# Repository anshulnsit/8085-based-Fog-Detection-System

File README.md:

# 8085-based-Fog-Detection-System
A Fog Detection system made with Intel 8085 microprocessor as EC - 316 Project

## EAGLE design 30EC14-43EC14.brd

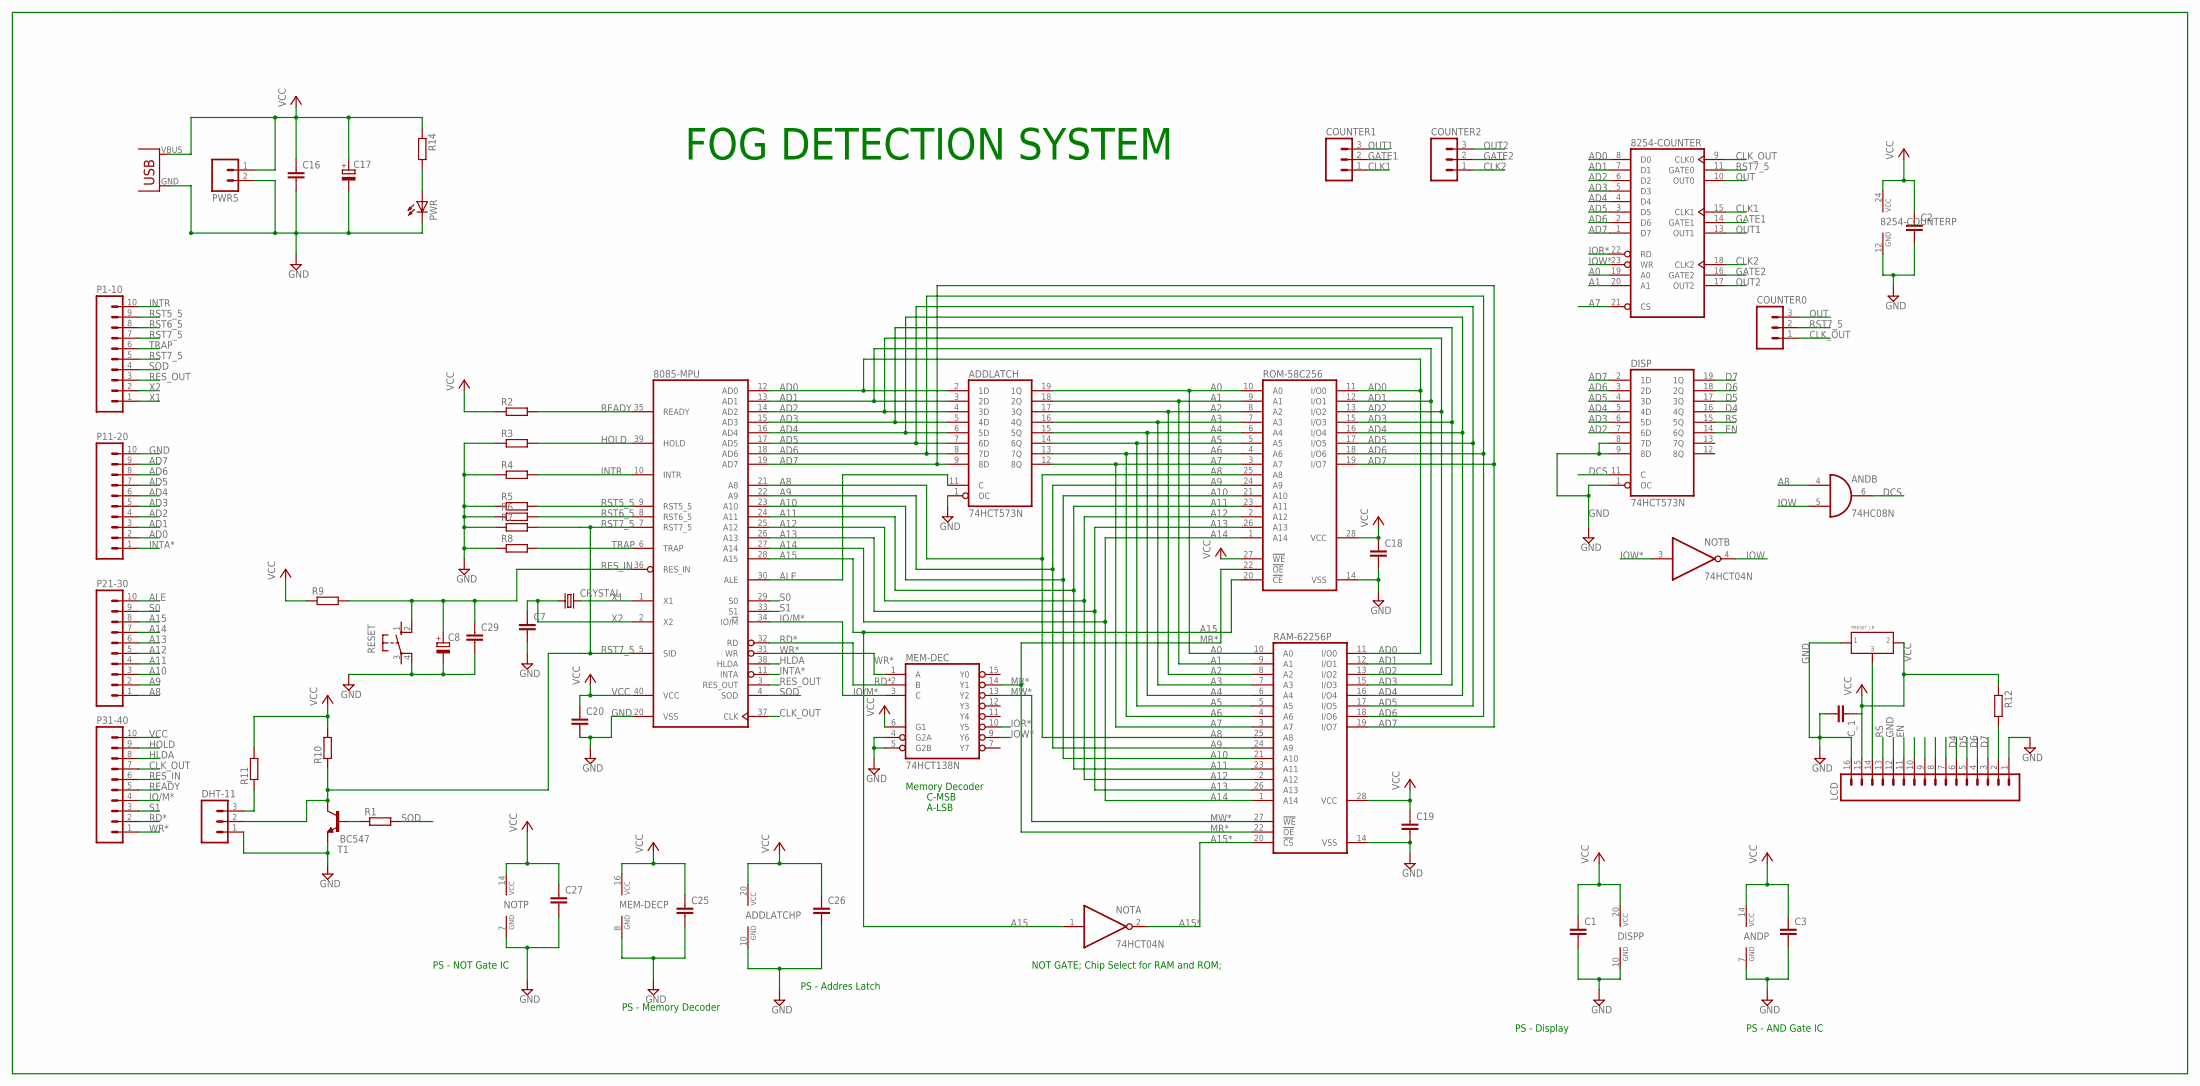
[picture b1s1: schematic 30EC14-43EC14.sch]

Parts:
8085-MPU: 8085; DIL40
8254-COUNTER: 8253; DIL24-6
ADDLATCH: 74HCT573N; DIL20
AND: 74HC08N; DIL14
C1, C2, C3, C7, C16, C18, C19, C20, C25, C26, C27, C29: C-EU025-025X050; C025-025X050
C8, C17: CPOL-EUE2.5-6; E2,5-6
COUNTER0, COUNTER1, COUNTER2: M03; 03P
CRYSTAL: CRYSTALHC49US; HC49US
C_1: C-EU025-024X044; C025-024X044
DHT-11: M03; 03P
DISP: 74HCT573N; DIL20
LCD: M16; 16P
MEM-DEC: 74HCT138N; DIL16
NOT: 74HCT04N; DIL14
P1-10, P11-20, P21-30, P31-40: M10; 10P
PWR: LED5MM
PWR5: M02; 02P
R1, R2, R3, R4, R5, R6, R7, R8, R9, R10, R11, R12, R14: R-EU_0204/7; 0204/7
RAM-62256P: 62256P; DIL28-6
RESET: 10-XX; B3F-10XX
ROM-58C256: 58C256P; DIL28-6
T1: BC547; TO92
U$1: PRESET_LR
USB: USB(POWER)

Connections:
A0: 8254-COUNTER.19 (A0), ADDLATCH.19 (1Q), RAM-62256P.10 (A0), ROM-58C256.10 (A0)
A1: 8254-COUNTER.20 (A1), ADDLATCH.18 (2Q), RAM-62256P.9 (A1), ROM-58C256.9 (A1)
A2: ADDLATCH.17 (3Q), RAM-62256P.8 (A2), ROM-58C256.8 (A2)
A3: ADDLATCH.16 (4Q), RAM-62256P.7 (A3), ROM-58C256.7 (A3)
A4: ADDLATCH.15 (5Q), RAM-62256P.6 (A4), ROM-58C256.6 (A4)
A5: ADDLATCH.14 (6Q), RAM-62256P.5 (A5), ROM-58C256.5 (A5)
A6: ADDLATCH.13 (7Q), RAM-62256P.4 (A6), ROM-58C256.4 (A6)
A7: 8254-COUNTER.21 (CS), ADDLATCH.12 (8Q), RAM-62256P.3 (A7), ROM-58C256.3 (A7)
A8: 8085-MPU.21 (A8), AND.4 (I0), P21-30.1, RAM-62256P.25 (A8), ROM-58C256.25 (A8)
A9: 8085-MPU.22 (A9), P21-30.2, RAM-62256P.24 (A9), ROM-58C256.24 (A9)
A10: 8085-MPU.23 (A10), P21-30.3, RAM-62256P.21 (A10), ROM-58C256.21 (A10)
A11: 8085-MPU.24 (A11), P21-30.4, RAM-62256P.23 (A11), ROM-58C256.23 (A11)
A12: 8085-MPU.25 (A12), P21-30.5, RAM-62256P.2 (A12), ROM-58C256.2 (A12)
A13: 8085-MPU.26 (A13), P21-30.6, RAM-62256P.26 (A13), ROM-58C256.26 (A13)
A14: 8085-MPU.27 (A14), P21-30.7, RAM-62256P.1 (A14), ROM-58C256.1 (A14)
A15: 8085-MPU.28 (A15), NOT.1 (I), P21-30.8, ROM-58C256.20 (!CE)
A15*: NOT.2 (O), RAM-62256P.20 (!CS)
AD0: 8085-MPU.12 (AD0), 8254-COUNTER.8 (D0), ADDLATCH.2 (1D), P11-20.2, RAM-62256P.11 (I/O0), ROM-58C256.11 (I/O0)
AD1: 8085-MPU.13 (AD1), 8254-COUNTER.7 (D1), ADDLATCH.3 (2D), P11-20.3, RAM-62256P.12 (I/O1), ROM-58C256.12 (I/O1)
AD2: 8085-MPU.14 (AD2), 8254-COUNTER.6 (D2), ADDLATCH.4 (3D), DISP.7 (6D), P11-20.4, RAM-62256P.13 (I/O2), ROM-58C256.13 (I/O2)
AD3: 8085-MPU.15 (AD3), 8254-COUNTER.5 (D3), ADDLATCH.5 (4D), DISP.6 (5D), P11-20.5, RAM-62256P.15 (I/O3), ROM-58C256.15 (I/O3)
AD4: 8085-MPU.16 (AD4), 8254-COUNTER.4 (D4), ADDLATCH.6 (5D), DISP.5 (4D), P11-20.6, RAM-62256P.16 (I/O4), ROM-58C256.16 (I/O4)
AD5: 8085-MPU.17 (AD5), 8254-COUNTER.3 (D5), ADDLATCH.7 (6D), DISP.4 (3D), P11-20.7, RAM-62256P.17 (I/O5), ROM-58C256.17 (I/O5)
AD6: 8085-MPU.18 (AD6), 8254-COUNTER.2 (D6), ADDLATCH.8 (7D), DISP.3 (2D), P11-20.8, RAM-62256P.18 (I/O6), ROM-58C256.18 (I/O6)
AD7: 8085-MPU.19 (AD7), 8254-COUNTER.1 (D7), ADDLATCH.9 (8D), DISP.2 (1D), P11-20.9, RAM-62256P.19 (I/O7), ROM-58C256.19 (I/O7)
ALE: 8085-MPU.30 (ALE), ADDLATCH.11 (C), P21-30.10
CLK1: 8254-COUNTER.15 (CLK1), COUNTER1.1
CLK2: 8254-COUNTER.18 (CLK2), COUNTER2.1
CLK_OUT: 8085-MPU.37 (CLK), 8254-COUNTER.9 (CLK0), COUNTER0.1, P31-40.7
D4: DISP.16 (4Q), LCD.6
D5: DISP.17 (3Q), LCD.5
D6: DISP.18 (2Q), LCD.4
D7: DISP.19 (1Q), LCD.3
DCS: AND.6 (O), DISP.11 (C)
EN: DISP.14 (6Q), LCD.11
GATE1: 8254-COUNTER.14 (GATE1), COUNTER1.2
GATE2: 8254-COUNTER.16 (GATE2), COUNTER2.2
GND: 8085-MPU.20 (VSS), 8254-COUNTER.12 (GND), ADDLATCH.1 (OC), ADDLATCH.10 (GND), AND.7 (GND), C1.2, C2.2, C3.2, C7.2, C8.-, C16.2, C17.-, C18.2, C19.2, C20.2, C25.2, C26.2, C27.2, C29.2, C_1.2, DHT-11.1, DISP.1 (OC), DISP.8 (7D), DISP.9 (8D), DISP.10 (GND), LCD.1, LCD.12, LCD.16, MEM-DEC.4 (G2A), MEM-DEC.5 (G2B), MEM-DEC.8 (GND), NOT.7 (GND), P11-20.10, PWR.K (C), PWR5.2, R3.1, R4.1, R5.1, R6.1, R7.1, R8.1, RAM-62256P.14 (VSS), RESET.4 (P1), ROM-58C256.14 (VSS), T1.1 (E), U$1.P$1 (1), USB.GND
HLDA: 8085-MPU.38 (HLDA), P31-40.8
HOLD: 8085-MPU.39 (HOLD), P31-40.9, R3.2
INTA*: 8085-MPU.11 (INTA), P11-20.1
INTR: 8085-MPU.10 (INTR), P1-10.10, R4.2
IO/M*: 8085-MPU.34 (IO/!M), MEM-DEC.3 (C), P31-40.4
IOR*: 8254-COUNTER.22 (RD), MEM-DEC.10 (Y5)
IOW: AND.5 (I1), NOT.4 (O)
IOW*: 8254-COUNTER.23 (WR), MEM-DEC.9 (Y6), NOT.3 (I)
MR*: MEM-DEC.14 (Y1), RAM-62256P.22 (!OE), ROM-58C256.22 (!OE)
MW*: MEM-DEC.13 (Y2), RAM-62256P.27 (!WE)
unnamed: LCD.14, U$1.P$3 (3)
unnamed: DHT-11.3, R11.1
unnamed: R1.1, T1.2 (B)
unnamed: LCD.2, R12.2
unnamed: PWR.A, R14.2
OUT: 8254-COUNTER.10 (OUT0), COUNTER0.3
OUT1: 8254-COUNTER.13 (OUT1), COUNTER1.3
OUT2: 8254-COUNTER.17 (OUT2), COUNTER2.3
RD*: 8085-MPU.32 (RD), MEM-DEC.2 (B), P31-40.2
READY: 8085-MPU.35 (READY), P31-40.5, R2.2
RES_IN: 8085-MPU.36 (RES_IN), C8.+, C29.1, P31-40.6, R9.2, RESET.2 (S1)
RES_OUT: 8085-MPU.3 (RES_OUT), P1-10.3
RS: DISP.15 (5Q), LCD.13
RST5_5: 8085-MPU.9 (RST5_5), P1-10.9, R5.2
RST6_5: 8085-MPU.8 (RST6_5), P1-10.8, R6.2
RST7_5: 8085-MPU.5 (SID), 8085-MPU.7 (RST7_5), 8254-COUNTER.11 (GATE0), COUNTER0.2, DHT-11.2, P1-10.5, P1-10.7, R7.2, R10.1, T1.3 (C)
S0: 8085-MPU.29 (S0), P21-30.9
S1: 8085-MPU.33 (S1), P31-40.3
SOD: 8085-MPU.4 (SOD), P1-10.4, R1.2
TRAP: 8085-MPU.6 (TRAP), P1-10.6, R8.2
VCC: 8085-MPU.40 (VCC), 8254-COUNTER.24 (VCC), ADDLATCH.20 (VCC), AND.14 (VCC), C1.1, C2.1, C3.1, C16.1, C17.+, C18.1, C19.1, C20.1, C25.1, C26.1, C27.1, C_1.1, DISP.20 (VCC), LCD.15, MEM-DEC.6 (G1), MEM-DEC.16 (VCC), NOT.14 (VCC), P31-40.10, PWR5.1, R2.1, R9.1, R10.2, R11.2, R12.1, R14.1, RAM-62256P.28 (VCC), ROM-58C256.27 (!WE), ROM-58C256.28 (VCC), U$1.P$2 (2), USB.VBUS (VCC)
WR*: 8085-MPU.31 (WR), MEM-DEC.1 (A), P31-40.1
X1: 8085-MPU.1 (X1), CRYSTAL.2, P1-10.1
X2: 8085-MPU.2 (X2), C7.1, CRYSTAL.1, P1-10.2

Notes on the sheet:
PS - NOT Gate IC
PS - Memory Decoder
PS - Addres Latch
Memory Decoder
C-MSB
A-LSB
NOT GATE; Chip Select for RAM and ROM;
PS - Display
PS - AND Gate IC
FOG DETECTION SYSTEM

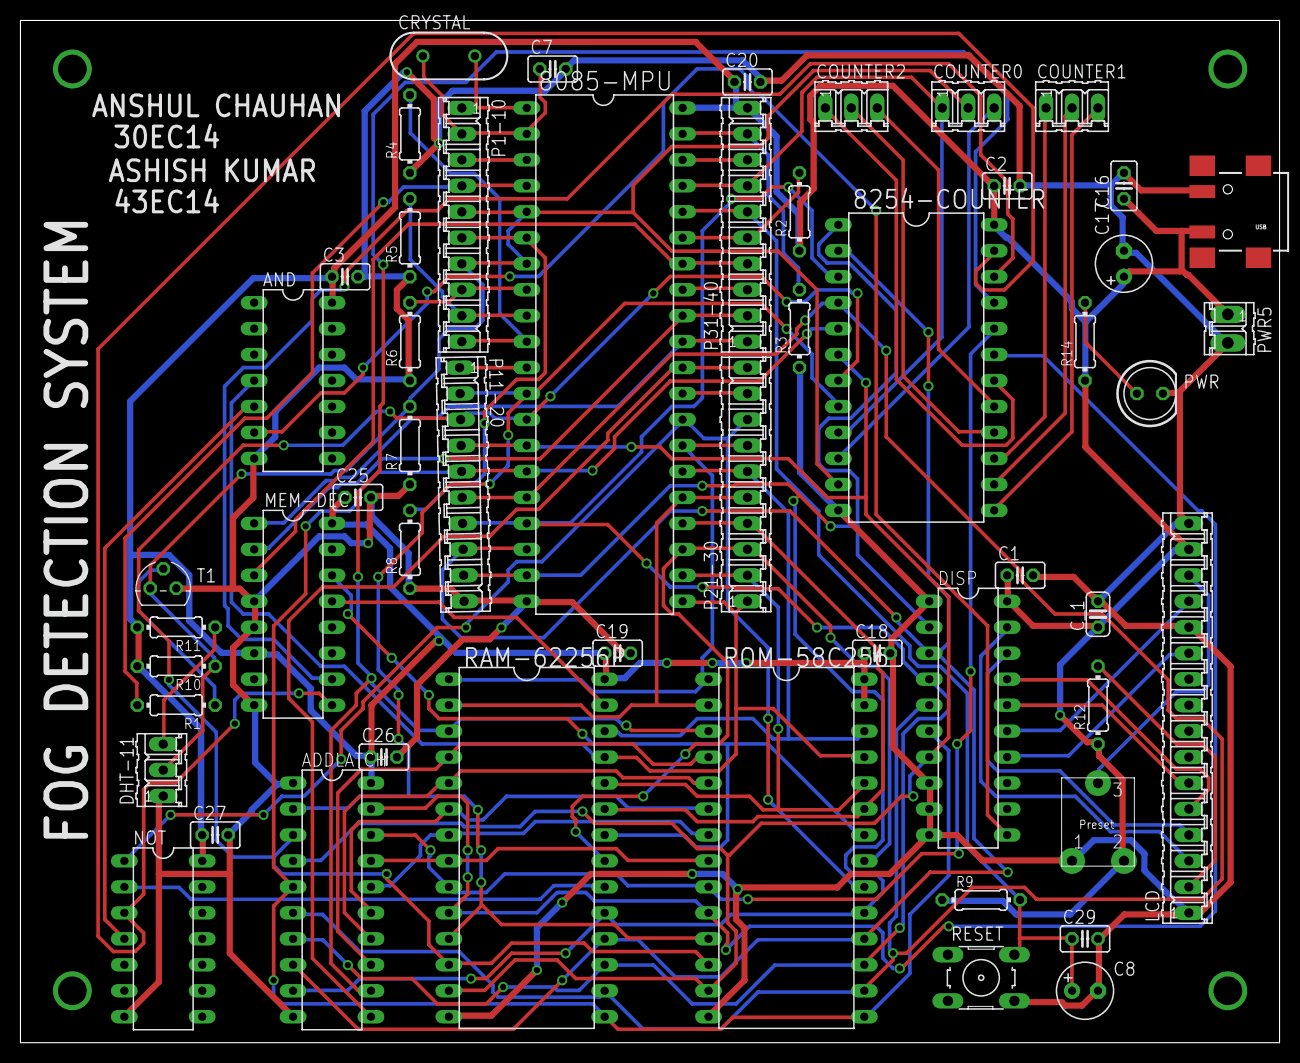
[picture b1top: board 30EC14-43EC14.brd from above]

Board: 2 copper layers, 123.2 x 100.0 mm, 53 parts (0 on the bottom side), 72 nets.

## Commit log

2017-05-25 Assembly Files
2017-05-29 Added schematic and board files
